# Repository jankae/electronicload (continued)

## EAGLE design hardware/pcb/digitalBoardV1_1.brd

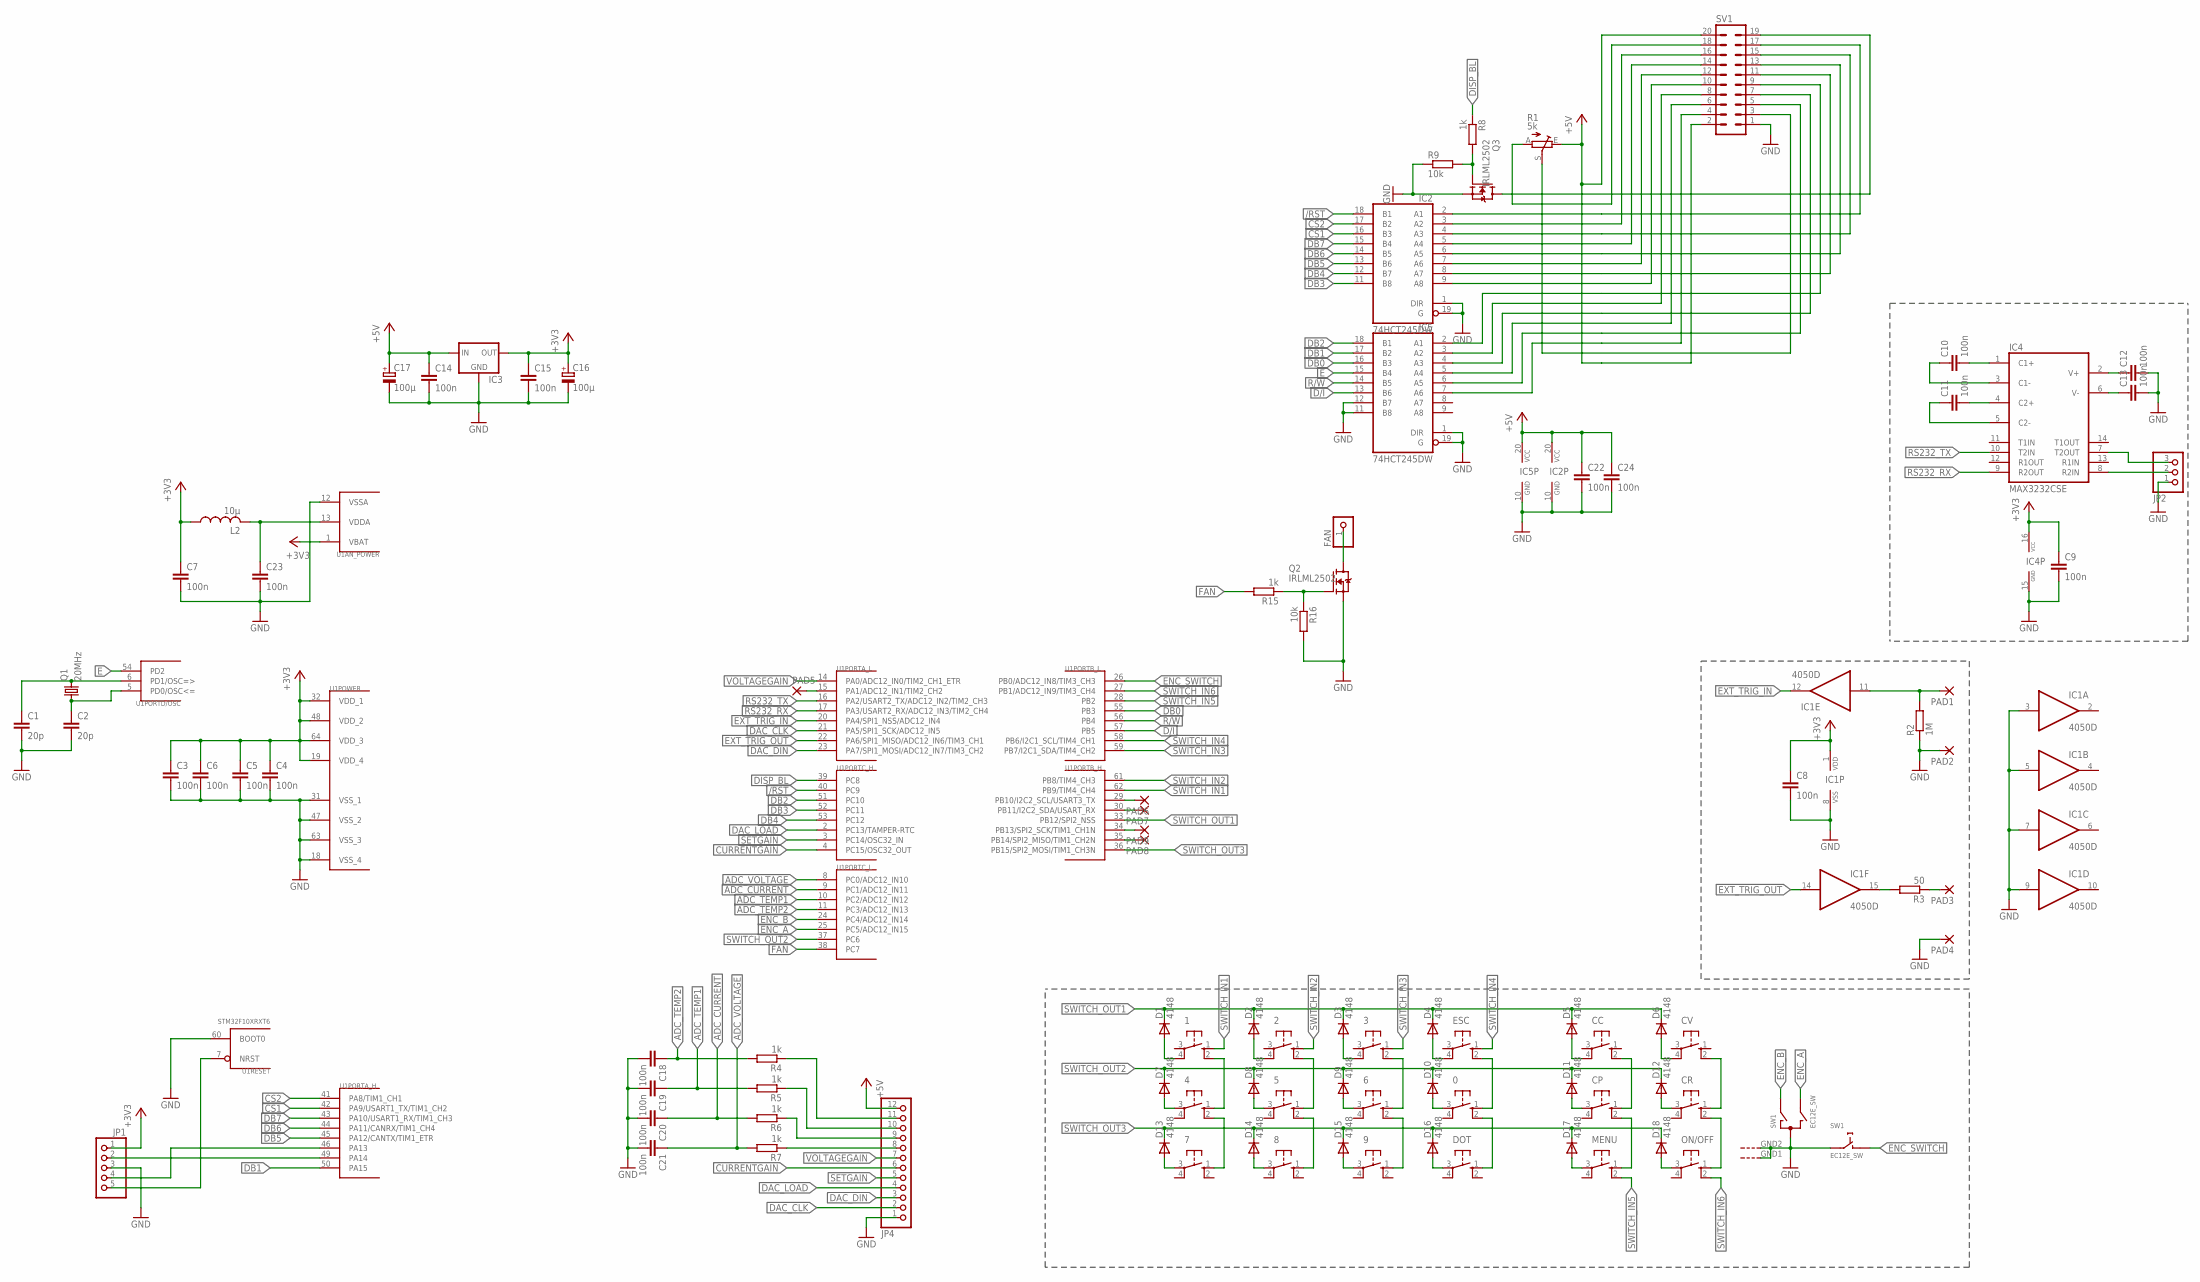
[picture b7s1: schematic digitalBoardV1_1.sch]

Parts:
0, 1, 2, 3, 4, 5, 6, 7, 8, 9: 10-XXSMD; SMD
C1, C2: 20p; C0603K
C3, C4, C5, C6, C7, C8, C9, C10, C11, C12, C13, C14, C15, C18, C19, C20, C21, C22, C23, C24: 100n; C0603K
C16, C17: 100µ; E2,5-6
CC: 10-XXSMD; SMD
CP: 10-XXSMD; SMD
CR: 10-XXSMD; SMD
CV: 10-XXSMD; SMD
D1, D2, D3, D4, D5, D6, D7, D8, D9, D10, D11, D12, D13, D14, D15, D16, D17, D18: 4148; SOD323-R
DOT: 10-XXSMD; SMD
ESC: 10-XXSMD; SMD
FAN: PINHD-1X1; 1X01
IC1: 4050D; SO16
IC2, IC5: 74HCT245DW; SO20W
IC3: LM1117; SOT223
IC4: MAX3232CSE; SO16
JP1: PINHD-1X5; 1X05
JP2: PINHD-1X3; 1X03
JP4: PINHD-1X12; 1X12
L2: 10µ; R0805
MENU: 10-XXSMD; SMD
ON/OFF: 10-XXSMD; SMD
PAD1, PAD2, PAD3, PAD4, PAD5, PAD6, PAD7, PAD8, PAD9: SMD2; SMD1,27-2,54
Q1: 20MHz; CTS406
Q2, Q3: IRLML2502; SOT23-3
R1: 5k; RJ9W
R2: 1M; R0603
R3: 50; R0603
R4, R5, R6, R7, R8, R15: 1k; R0603
R9, R16: 10k; R0603
SV1: ML20
SW1: EC12E_SW; ALPS_EC12E_SW
U1: STM32F10XRXT6; TQFP64

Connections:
+3V3: C3.1, C4.1, C5.1, C6.1, C7.1, C8.1, C9.1, C15.1, C16.+, IC1.1 (VDD), IC3.2 (OUT), IC4.16 (VCC), JP1.1, L2.1, U1.1 (VBAT), U1.19 (VDD_4), U1.32 (VDD_1), U1.48 (VDD_2), U1.64 (VDD_3)
+5V: C14.1, C17.+, C22.1, C24.1, IC2.20 (VCC), IC3.3 (IN), IC5.20 (VCC), JP4.12, R1.E, SV1.2, SV1.20
/RST: IC2.18 (B1), U1.40 (PC9)
ADC_CURRENT: C20.1, R6.2, U1.9 (PC1/ADC12_IN11)
ADC_TEMP1: C19.1, R5.2, U1.10 (PC2/ADC12_IN12)
ADC_TEMP2: C18.1, R4.2, U1.11 (PC3/ADC12_IN13)
ADC_VOLTAGE: C21.1, R7.2, U1.8 (PC0/ADC12_IN10)
CS1: IC2.16 (B3), U1.42 (PA9/USART1_TX/TIM1_CH2)
CS2: IC2.17 (B2), U1.41 (PA8/TIM1_CH1)
CURRENTGAIN: JP4.6, U1.4 (PC15/OSC32_OUT)
D/I: IC5.13 (B6), U1.57 (PB5)
DAC_CLK: JP4.2, U1.21 (PA5/SPI1_SCK/ADC12_IN5)
DAC_DIN: JP4.3, U1.23 (PA7/SPI1_MOSI/ADC12_IN7/TIM3_CH2)
DAC_LOAD: JP4.4, U1.2 (PC13/TAMPER-RTC)
DB0: IC5.16 (B3), U1.55 (PB3)
DB1: IC5.17 (B2), U1.50 (PA15)
DB2: IC5.18 (B1), U1.51 (PC10)
DB3: IC2.11 (B8), U1.52 (PC11)
DB4: IC2.12 (B7), U1.53 (PC12)
DB5: IC2.13 (B6), U1.45 (PA12/CANTX/TIM1_ETR)
DB6: IC2.14 (B5), U1.44 (PA11/CANRX/TIM1_CH4)
DB7: IC2.15 (B4), U1.43 (PA10/USART1_RX/TIM1_CH3)
DISP_BL: R8.1, U1.39 (PC8)
E: IC5.15 (B4), U1.54 (PD2)
ENC_A: SW1.B, U1.25 (PC5/ADC12_IN15)
ENC_B: SW1.A, U1.24 (PC4/ADC12_IN14)
ENC_SWITCH: SW1.D (1), U1.26 (PB0/ADC12_IN8/TIM3_CH3)
EXT_TRIG_IN: IC1.12 (O), U1.20 (PA4/SPI1_NSS/ADC12_IN4)
EXT_TRIG_OUT: IC1.14 (I), U1.22 (PA6/SPI1_MISO/ADC12_IN6/TIM3_CH1)
FAN: R15.2, U1.38 (PC7)
GND: C1.2, C2.2, C3.2, C4.2, C5.2, C6.2, C7.2, C8.2, C9.2, C12.2, C13.2, C14.2, C15.2, C16.-, C17.-, C18.2, C19.2, C20.2, C21.2, C22.2, C23.2, C24.2, IC1.3 (I), IC1.5 (I), IC1.7 (I), IC1.8 (VSS), IC1.9 (I), IC2.1 (DIR), IC2.10 (GND), IC2.19 (G), IC3.1 (GND), IC4.15 (GND), IC5.1 (DIR), IC5.10 (GND), IC5.11 (B8), IC5.12 (B7), IC5.19 (G), JP1.3, JP2.1, JP4.1, PAD2.1, PAD4.1, Q2.2 (S), Q3.2 (S), R2.1, R9.1, R16.2, SV1.1, SW1.C, SW1.E (2), SW1.GND1 (G), SW1.GND2 (G), U1.12 (VSSA), U1.18 (VSS_4), U1.31 (VSS_1), U1.47 (VSS_2), U1.60 (BOOT0), U1.63 (VSS_3)
unnamed: C1.1, Q1.3 (2), U1.6 (PD1/OSC=>)
unnamed: C2.1, Q1.1, U1.5 (PD0/OSC<=)
unnamed: IC1.11 (I), PAD1.1, R2.2
unnamed: IC1.15 (O), R3.2
unnamed: PAD3.1, R3.1
unnamed: C10.2, IC4.1 (C1+)
unnamed: C10.1, IC4.3 (C1-)
unnamed: C11.2, IC4.4 (C2+)
unnamed: C11.1, IC4.5 (C2-)
unnamed: C13.1, IC4.6 (V-)
unnamed: C12.1, IC4.2 (V+)
unnamed: JP4.8, R7.1
unnamed: JP4.9, R6.1
unnamed: R1.A, SV1.18
unnamed: JP4.10, R5.1
unnamed: JP4.11, R4.1
unnamed: 0.1 (S), ESC.2 (S1)
unnamed: 0.2 (S1), DOT.1 (S)
unnamed: C23.1, L2.2, U1.13 (VDDA)
unnamed: IC4.8 (R2IN), JP2.2
unnamed: 4.2 (S1), 7.1 (S)
unnamed: 1.2 (S1), 4.1 (S)
unnamed: 2.2 (S1), 5.1 (S)
unnamed: 5.2 (S1), 8.1 (S)
unnamed: 3.2 (S1), 6.1 (S)
unnamed: 6.2 (S1), 9.1 (S)
unnamed: CC.2 (S1), CP.1 (S)
unnamed: CP.2 (S1), MENU.1 (S)
unnamed: CR.1 (S), CV.2 (S1)
unnamed: CR.2 (S1), ON/OFF.1 (S)
unnamed: IC4.7 (T2OUT), JP2.3
unnamed: 1.4 (P1), D1.A
unnamed: 2.4 (P1), D2.A
unnamed: 3.4 (P1), D3.A
unnamed: D4.A, ESC.4 (P1)
unnamed: CC.4 (P1), D5.A
unnamed: CV.4 (P1), D6.A
unnamed: 4.3, D7.A
unnamed: 7.3, D13.A
unnamed: 8.3, D14.A
unnamed: 5.3, D8.A
unnamed: 6.3, D9.A
unnamed: 9.3, D15.A
unnamed: D16.A, DOT.3
unnamed: PAD9.1, U1.34 (PB13/SPI2_SCK/TIM1_CH1N)
unnamed: 0.3, D10.A
unnamed: CP.3, D11.A
unnamed: D17.A, MENU.3
unnamed: PAD8.1, U1.35 (PB14/SPI2_MISO/TIM1_CH2N)
unnamed: Q2.1 (G), R15.1, R16.1
unnamed: FAN.1, Q2.3 (D)
unnamed: D18.A, ON/OFF.3
unnamed: CR.3, D12.A
unnamed: R1.S, SV1.3
unnamed: Q3.1 (G), R8.2, R9.2
unnamed: IC2.2 (A1), SV1.17
unnamed: IC2.3 (A2), SV1.16
unnamed: IC2.4 (A3), SV1.15
unnamed: IC2.5 (A4), SV1.14
unnamed: IC2.6 (A5), SV1.13
unnamed: IC2.7 (A6), SV1.12
unnamed: IC2.8 (A7), SV1.11
unnamed: IC2.9 (A8), SV1.10
unnamed: IC5.2 (A1), SV1.9
unnamed: IC5.3 (A2), SV1.8
unnamed: IC5.4 (A3), SV1.7
unnamed: IC5.5 (A4), SV1.6
unnamed: IC5.6 (A5), SV1.5
unnamed: Q3.3 (D), SV1.19
unnamed: IC5.7 (A6), SV1.4
unnamed: PAD7.1, U1.30 (PB11/I2C2_SDA/USART_RX)
unnamed: PAD6.1, U1.29 (PB10/I2C2_SCL/USART3_TX)
unnamed: PAD5.1, U1.15 (PA1/ADC12_IN1/TIM2_CH2)
NRST: JP1.5, U1.7 (NRST)
R/W: IC5.14 (B5), U1.56 (PB4)
RS232_RX: IC4.9 (R2OUT), U1.17 (PA3/USART2_RX/ADC12_IN3/TIM2_CH4)
RS232_TX: IC4.10 (T2IN), U1.16 (PA2/USART2_TX/ADC12_IN2/TIM2_CH3)
SETGAIN: JP4.5, U1.3 (PC14/OSC32_IN)
SWCLK: JP1.2, U1.49 (PA14)
SWDIO: JP1.4, U1.46 (PA13)
SWITCH_IN1: 1.1 (S), U1.62 (PB9/TIM4_CH4)
SWITCH_IN2: 2.1 (S), U1.61 (PB8/TIM4_CH3)
SWITCH_IN3: 3.1 (S), U1.59 (PB7/I2C1_SDA/TIM4_CH2)
SWITCH_IN4: ESC.1 (S), U1.58 (PB6/I2C1_SCL/TIM4_CH1)
SWITCH_IN5: MENU.2 (S1), U1.28 (PB2)
SWITCH_IN6: ON/OFF.2 (S1), U1.27 (PB1/ADC12_IN9/TIM3_CH4)
SWITCH_OUT1: D1.C, D2.C, D3.C, D4.C, D5.C, D6.C, U1.33 (PB12/SPI2_NSS)
SWITCH_OUT2: D7.C, D8.C, D9.C, D10.C, D11.C, D12.C, U1.37 (PC6)
SWITCH_OUT3: D13.C, D14.C, D15.C, D16.C, D17.C, D18.C, U1.36 (PB15/SPI2_MOSI/TIM1_CH3N)
VOLTAGEGAIN: JP4.7, U1.14 (PA0/ADC12_IN0/TIM2_CH1_ETR)

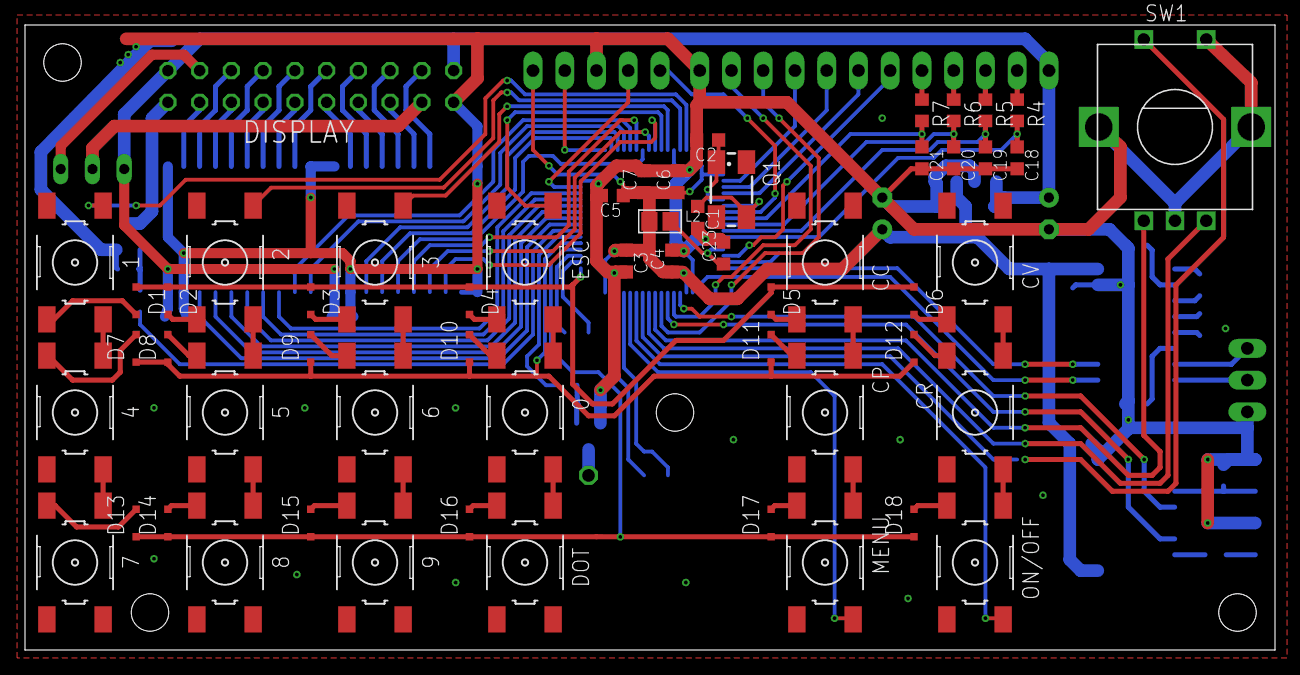
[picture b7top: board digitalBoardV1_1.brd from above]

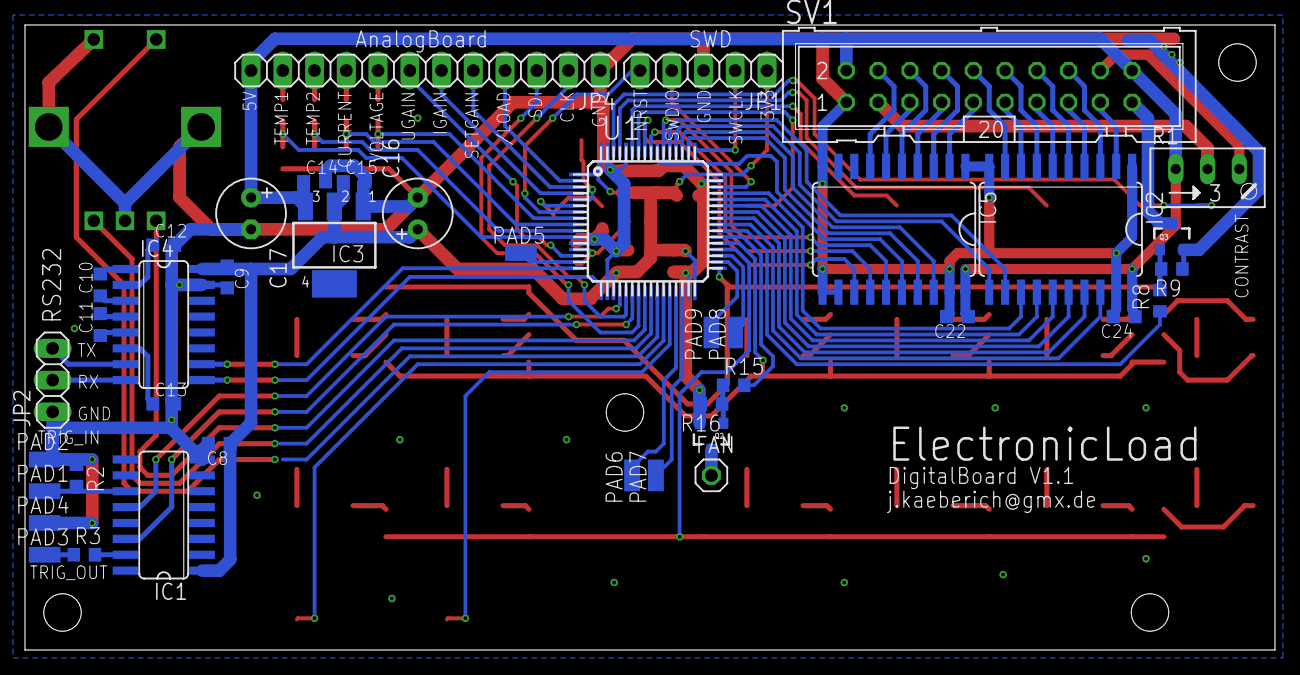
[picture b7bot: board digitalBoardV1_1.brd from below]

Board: 2 copper layers, 100.0 x 50.0 mm, 96 parts (41 on the bottom side), 121 nets.

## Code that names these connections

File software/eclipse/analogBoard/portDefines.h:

#define DDR_SHUNT_EN2       DDRB
#define PORT_SHUNT_EN2      PORTB
#define BIT_SHUNT_EN2       PB1

#define DDR_SHUNT_EN1       DDRB
#define PORT_SHUNT_EN1      PORTB
#define BIT_SHUNT_EN1       PB0

#define DDR_SHUNT_SEL       DDRD
#define PORT_SHUNT_SEL      PORTD
#define BIT_SHUNT_SEL       PD7

#define DDR_MODE_A          DDRD
#define PORT_MODE_A         PORTD
#define BIT_MODE_A          PD4

#define DDR_MODE_B          DDRD
#define PORT_MODE_B         PORTD
#define BIT_MODE_B          PD3

#define DDR_ANALOG_MUX      DDRD
#define PORT_ANALOG_MUX     PORTD
#define BIT_ANALOG_MUX      PD2

#define DDR_GPIO3           DDRD
#define PORT_GPIO3          PORTD
#define BIT_GPIO3           PD5

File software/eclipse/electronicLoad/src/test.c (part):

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    uint8_t gpios = 0;
    uint8_t active = 1;

    char gpioNames[7][12] = { "1:SHUNT_EN2", "2:SHUNT_EN1", "3:SHUNTSEL",
            "4:GPIO3", "5:MODE_A", "6:MODE_B", "7:ANA_MUX" };
    do {
        screen_Clear();
        screen_FastString6x8("Manual GPIO control", 0, 0);
        // display current GPIO status
        uint8_t i;
        uint8_t j = 1;
        for (i = 0; i < 7; i++) {
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
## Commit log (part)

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2016-02-01 initial commit hardware
2016-02-01 initial commit software
2016-02-01 eclipse project files
2016-02-01 removed settings folder
2016-02-01 removed build file
2016-02-01 remove Release folder
2016-02-01 add gitignore files
2016-02-01 added main.h
2016-02-01 added config section at end of flash in linker script
2016-02-01 added calibration read and write routines for flash values
2016-02-01 added default calibration values
2016-02-01 changed frontpanel button from enum to bitmask (allows detection of multiple buttons pressed at the same time)
2016-02-01 doxygen config
2016-02-01 Doxygen comments
2016-02-02 changed displayRoutines to screen
2016-02-02 doxygen documentation
2016-02-02 moved MS_TO_TICKS macro from main to timer
2016-02-02 frontpanel hal code
2016-02-02 doxygen documentation + using timer1 as systemclock
2016-02-02 moved callback registration for update_loadfunction from main to loadfunction_init
2016-02-02 added wait time for ADC settling
2016-02-02 added string terminator
2016-02-02 added timeout functionality
2016-02-02 started menu files
2016-02-02 added HAL_BUTTON_ISDIGIT mask
2016-02-02 changed tabs to spaces
2016-02-02 added default screen line set function
2016-02-02 renamed loadfunctions.type to mode
2016-02-02 added power off functionality
2016-02-02 added default screen menu
2016-02-03 minimum load parameter values
2016-02-03 encoder movement handling in default screen
2016-02-03 added calibration menu to main menu
2016-02-04 loadType_t -> loadMode_t
2016-02-04 function for changing load mode without specifying mode parameter
2016-02-04 create event files
2016-02-07 display RST pin change due to botched up solder job
2016-02-07 clear timer interrupt bit
2016-02-07 hardware system interrupt handlers
2016-02-08 changed clock to 16Mhz crystal
2016-02-08 bugfix initialising GPIOs
2016-02-08 bugfix: made timer.ms volatile
2016-02-08 bugfix: changed setPixel function according to new buffer layout
2016-02-08 changed ADC channels to correct values, added macros for DAC GPIOs
2016-02-08 moved jtag disable command into main.c
2016-02-08 added encoder sensitivity setting. Also changed DAC update frequency to 2kHz
2016-02-08 bugfix prescaler calculation
2016-02-08 updated menu messages
2016-02-08 mode parameters are now signed
2016-02-08 changed update frequency
2016-02-08 added temperature to default screen. Also fixed bug in power calculation
2016-02-11 changed external input trigger mode from interrupt to polling
2016-02-11 corrected ADC channel order
2016-02-11 added external trigger handling + init function
2016-02-11 added event handling in the load update interrupt
2016-02-11 added events initialization
2016-02-11 new sub menu dialog: item chooser
    -implemented main menu using the item chooser menu
2016-02-11 added event list menu
2016-02-11 added string copy function
2016-02-11 added event menu to main menu
2016-02-12 force values for enumeration
2016-02-12 functions for copying strings
2016-02-12 bugfix: don't allow dots for integers without fixed point
2016-02-12 event edit and display menus
2016-02-21 Frontpanel layout
2016-02-25 omitted hardware trimmer calibration
2016-02-25 rename loadFunction struct to load, added global state variables
2016-02-25 set available digits in main screen to 5 (was 6)
2016-02-25 included calibration reading at startup
2016-02-25 default screen uses global load state variables
2016-02-25 added fan control + overtemperature shutdown
2016-02-25 bugfix temperature scale
2016-02-25 bugfix number of displayed digits
2016-02-28 various bugfixes + adjusted calibration process
2016-02-28 position of load parameter adjusted
2016-03-03 display content will only be updated after a certain time without change
2016-03-03 uart hal added (+ some test ouputs in main)
2016-03-03 update default screen regularly even without user input (events may have changed values)
2016-03-03 fixed powerOn/powerOff events
2016-03-03 new eclipse project settings
2016-03-04 completed intialization of event structs
2016-03-04 added basic debouncing for frontpanel switches
2016-03-08 removed calibration section in linker script, instead working with FLASH adresses directly (calibration won't be lost during programming anymore)
2016-03-08 using average values on main screen
2016-03-08 avg values on main screen
2016-03-08 added statistics menu
2016-03-08 uart recieve functionality
2016-03-08 combining load_update and hal_frontpanelupdate to free timer 4
2016-03-08 inWritePos now uint8
2016-03-08 basic uart commands
2016-03-08 custom string compare function
2016-03-08 added a few uart commands
2016-03-08 terminate uart retrieve string
2016-03-08 minor changes just to remove some warnings
2016-03-21 drawing lines
2016-03-21 hal_frontPanelUpdate even when calibration is active
2016-03-21 progress bar during ADC sampling
2016-03-21 new analogBoard
2016-03-21 a few mechanical changes
2016-05-06 disable waveform on constant setting
2016-05-06 bugfixes waveforms
2016-05-06 switch off waveforms in constant modes and vice-versa
2016-05-07 waveform phase can be used as event trigger + minor bugfixes
2016-05-09 encoder sensitivity is now changeable
2016-05-09 added Bresenham algorithm for diagonal lines
2016-05-09 started common functions file, so far only with a mapping function
2016-05-09 waveform representation with lines instead with pixels
2016-05-09 new feature: I/U characterisation
2016-05-09 bugfix: wrong current values during high-to-low ramp
2016-05-10 sending measurement results via uart
2016-07-10 bugfix: swapped buttons
2016-07-10 baudrate settable via uart_init
2016-07-10 implemented basic settings menu (not tested)
2016-07-10 added busy flag indicating uart transmission
2016-07-10 actual change the uart baudrate
2016-07-17 added BOM
2016-07-22 calibration changed: voltage can be specified (within limits)
2016-07-22 menu-settable current/power/voltage/resistance limits
2016-09-09 analog version update
2016-09-09 cleaned up schematics + markings an analogBoard
2016-09-12 a lot of changes:
    - multimeter integration (UT61E) for automatic calibration
    - added soft buttons
    - input dialog adapted to accept different units
2016-09-12 more sophisticated uint to string conversion function
2016-09-14 further adaptions to new version !not compilable!
2016-09-14 BOM for new analog board design
2016-09-14 glue logic firmware analog board
2016-09-14 removed old .gitignore
2016-09-14 added internal bandgap voltage to ADC channels
2016-09-14 temporarily commented a lot of code to make it compilable
2016-09-14 rename to keep consistent
2016-09-14 selftest at startup
2016-09-14 hardware calibration procedure added
2016-09-15 corrected page number
2016-09-15 redesign statistics menu
2016-09-15 further adaptions to new HW version
2016-09-15 default screen layout refined
2016-09-16 different limits in low/high power mode
2016-09-16 adjustments for different fixed integer algorithmik
2016-09-16 adjusted unit display on result viewer
2016-09-16 a bit of everything ;)
2016-09-17 mostly calibration stuff
2016-09-17 more calibration stuff
2016-09-17 calibration reduced to two point calibration
2016-09-17 default calibration added
2016-09-18 automatic calibration nearly completed
2016-09-18 resistance calibration added
2016-09-18 bugfix: wrong usage of calibration points
2016-09-18 bugfix: got rid of extra space in case dot=0
2016-09-18 included temperature in main screen
2016-09-20 SPI timing fixes
    - additional delay for AVR added
    - optional Assembler routines for DAC and ADC
2016-09-20 some tests for buttons and the ascii font (+easter egg)
2016-09-22 analog board fixes
    - enabled interrupts
    - moved ADC evaluation from interrupt into main (was interfering with
    SPI timing)
2016-09-22 various bugfixes in communication with analog board
    - additional delay between SPI bytes (allow time for interrupt in AVR)
    - read rails now reading from correct ADC channels
2016-09-22 more tests, mainly for testing communication with analog board
2016-09-24 set ports directly in SPI interrupts -> less jitter on the port delay
2016-09-24 bugfix: too many chars if using prefix + displaying dot
2016-09-24 test functions for ADC and DAC
2016-09-24 bugfix: map calcultion was not working at all
2016-09-24 ADC averaging
2016-09-24 fixed formatting
2016-09-24 default calibration adjusted to new resistor value
2016-09-24 relaxed timing on AVR (might work faster but this eliminated wrong data)
2016-09-25 position of '-' sign adjusted
2016-09-25 display: clear at startup
2016-09-25 ADC + DAC calls corrected
2016-09-25 give AVR more time to start (more accurate selftest voltages)
2016-09-26 number of maximum ADC samples increased
2016-09-26 some bugfixes in calibration routine + split of calibration struct
2016-09-29 always update DAC
2016-09-29 more precise communication
    Don't change amount of communication with analog board during
    calibration -> less deviation due to digital feedtrough
2016-10-07 oscillation detection using ADC
2016-10-07 bugfix: disable IO control during some tests
2016-10-08 set SPI MOSI low when not in use (got rid of strange miscommunications)
2016-10-09 save selected menu entry while navigating backwards
2016-10-09 bugfix: write CAL_INDICATOR instead hard-coded 0x01
2016-10-09 save settings in FLASH and load at startup
2016-10-09 no analog and digital control available in CR and CP
2016-10-09 various bugfixes for analog/digital control modes
2016-10-11 ADC unstable function extended
2016-10-11 ADC averaging and checking for unstable condition
2016-10-11 hardware calibration updated
2016-10-11 check ALL trigger sources first THEN trigger destinations
2016-10-11 parameter order changed for screen_FastChar
2016-10-11 automatic turn off if error occurs (TODO: reset errors in menu)
2016-10-12 moved error handling into dedicated file
2016-10-12 debugging: error detection and displaying
2016-10-12 use screen_text in calibration messages
2016-10-12 turn all mosfets off if error present
2016-10-22 Fan controlled from digital board
2016-10-22 additional errors plus longer delay on error condition
2016-10-22 higher fan threshold
2016-10-22 CP and CR always digitally controlled
2016-10-24 increased maximum allowed current while switched off
2016-10-24 calibration splitted into multiple small calibration routines
2016-10-24 waveform phase calculation continuous even if period is changed
2016-10-24 UNTESTED: event menu slightly improved
2016-10-24 case/switch instead of ifs
2016-10-24 multiple effects possible on every event
2016-10-24 additional string display function
2016-10-24 nicer display of values + maximum allowed value increased
2016-10-25 arbitrary sequence edit menu
2016-10-25 missing files to previous commit
2016-10-26 enter value by digits implemented
2016-10-27 arbitrary sequences nearly completed
2016-10-29 eclipse project settings
2016-10-29 error duration reduced again
2016-10-29 voltage calibration completed
2016-11-06 update trigger out directly after setting DAC
2017-01-29 label widget and container editing mode added
2017-01-29 change callback
2017-01-29 drawing done by widget functions instead of centralized drawing function
2017-01-29 label drawing + selectable fixed
2017-01-29 invertRectangle -> fullRectangle (either on/off or invert)
2017-01-29 bugfix PIXEL_ON -> PIXEL_INVERT
2017-01-29 draw selected child always last
2017-01-29 dropdown menu widget added
2017-01-29 notebook widget added
2017-01-29 automatic button size based on font
2017-01-30 scrollbars added to container
2017-01-30 linelength fixed
2017-01-30 label with local name storage
2017-01-30 extensive changes
    - GUI message box
    - common settings for high and low power mode
    - settings menu using new GUI
2017-01-30 U/I characteristics with new GUI
2017-01-30 waveform menu adapted
2017-01-30 Checkbox widget
2017-01-30 Calibration menu moved
2017-01-31 Arbitrary menu adapted
2017-02-05 display only entry: valueLabel
2017-02-06 main menu functional
2017-02-06 new waveform: reverse saw
2017-02-07 'turn off on error' setting added
2017-02-07 Few bugfixes + beginning of event menu
2017-02-08 event menu completed, number of warning reduced
2017-03-10 Changed to new Eclipse version
